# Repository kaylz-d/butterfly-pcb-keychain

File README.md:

# This is a design of a butterfly PCB keychain!

I'm submitting it for Solder by Hack Club.
The butterfly shape is based on resin shaker keychains that were somewhat popular for a bit during quarantine. I followed the shape of the resin shaker mold, making a butterfly SVG vector in Figma that I put on the Edge Cuts layer, making the PCB design in KiCad. This design is 89.1418 mm x 70.5458 mm.

When you push the button, the LEDs will light up. You can control the brightness of the LEDs with the potentiometer.

## Materials
- Battery Holder (1)
- Push Button (1)
- LED 5.0mm (2)
- 220 Resistor (3)
- NPN Transistor (2)
- Potentiometer (1)

## Schematic

## PCB

## 3D View: Front

## 3D View: Back

Made by `@Kaylee` on slack

Made for http://solder.hackclub.com/ and https://highway.hackclub.com/

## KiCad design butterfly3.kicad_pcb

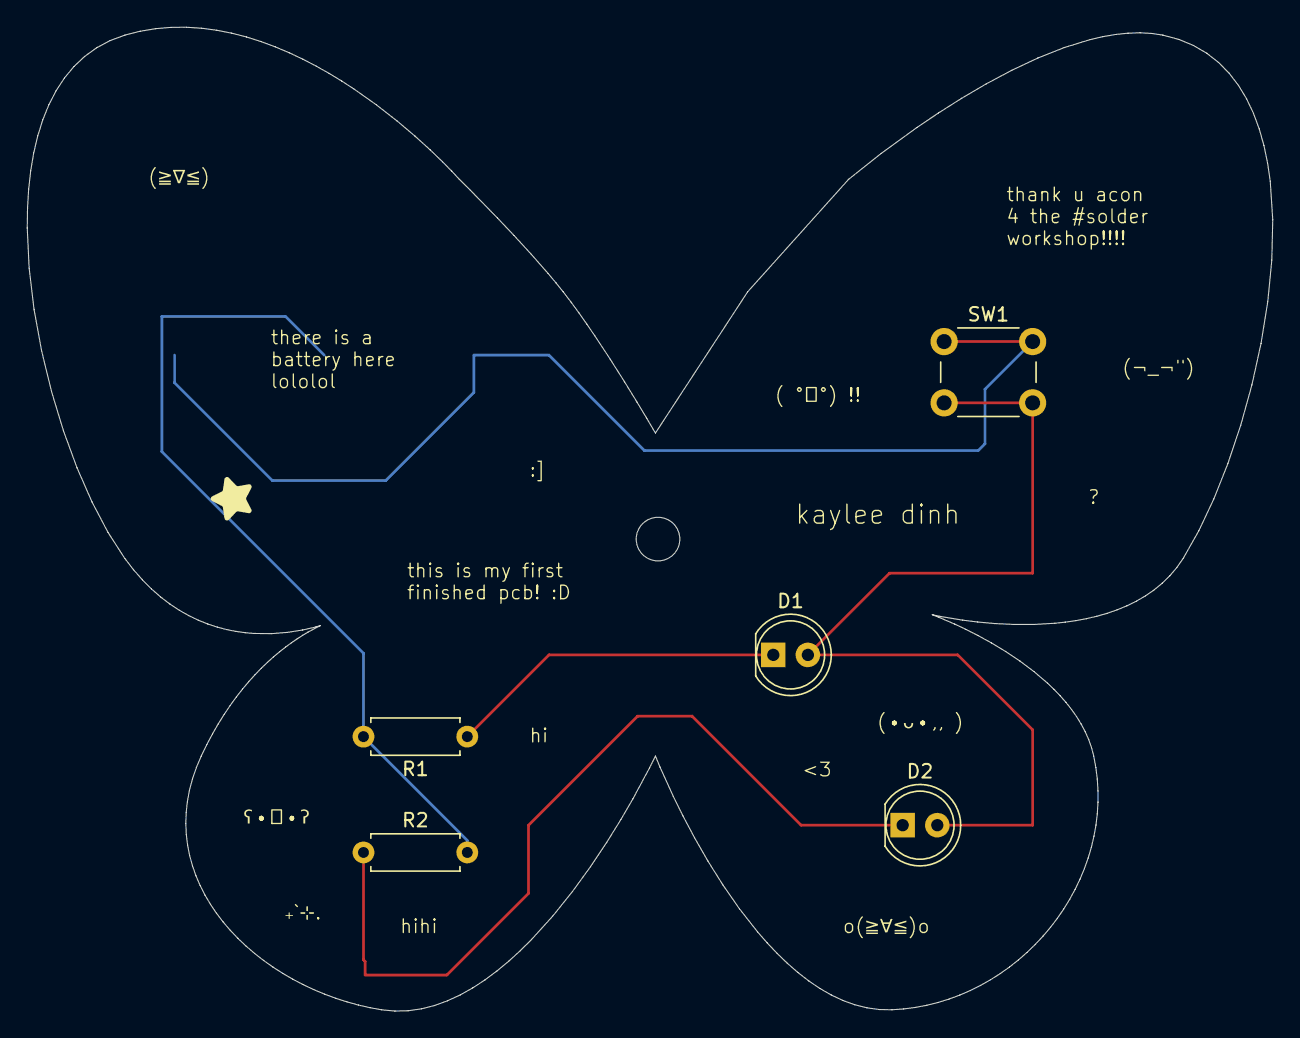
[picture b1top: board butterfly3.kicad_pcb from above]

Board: 2 copper layers, 91.4 x 72.2 mm, 6 parts (1 on the bottom side), 5 nets.

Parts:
BT1: Battery_Cell; BatteryHolder_Keystone_3034_1x20mm
D1, D2: LED; LED_D5.0mm
R1, R2: 220; R_Axial_DIN0207_L6.3mm_D2.5mm_P7.62mm_Horizontal
SW1: SW_Push; SW_PUSH_6mm

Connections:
unnamed: BT1.1 (+), SW1.1
unnamed: BT1.2 (-), R1.2, R2.2
unnamed: D1.2 (A), D2.2 (A), SW1.2
unnamed: D1.1 (K), R1.1
unnamed: D2.1 (K), R2.1
